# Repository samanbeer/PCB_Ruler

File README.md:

## 30 cm PCB Ruler
https://FORGE.hackclub.com/projects/1713

Why:
- Is is cool, the schooll is coming :O and i dont have a ruler :)

Schematic is randomly connected so it looks good on PCB (not supposed to work :D):

This is a Ruler made as PCB in KiCAD and InkScape(for .svg editing).

- Every design file is in /images folder. 
- And anyone can modify the PCB Ruler by opening This KiCad project in KiCAD v10+
- For direct manufacturing, the gerber files .zip is in /gerbers folder
- Cost around 10 US Dollars :)

Here is JLCPCB cart:

Rendered Image:

## BOM:

| What                             | PRICE    |
| -------------------------------- | -------- |
| PCB (Ruler) + shipping + Customs | 17.15 USD |

*note: I dont need components since I will not solder them on the ruler. The components footprints are for <u>design</u>*

## Builded  project:

Detailed photos:

The precision is great, at the end it has offest just by 0.5mm which is great

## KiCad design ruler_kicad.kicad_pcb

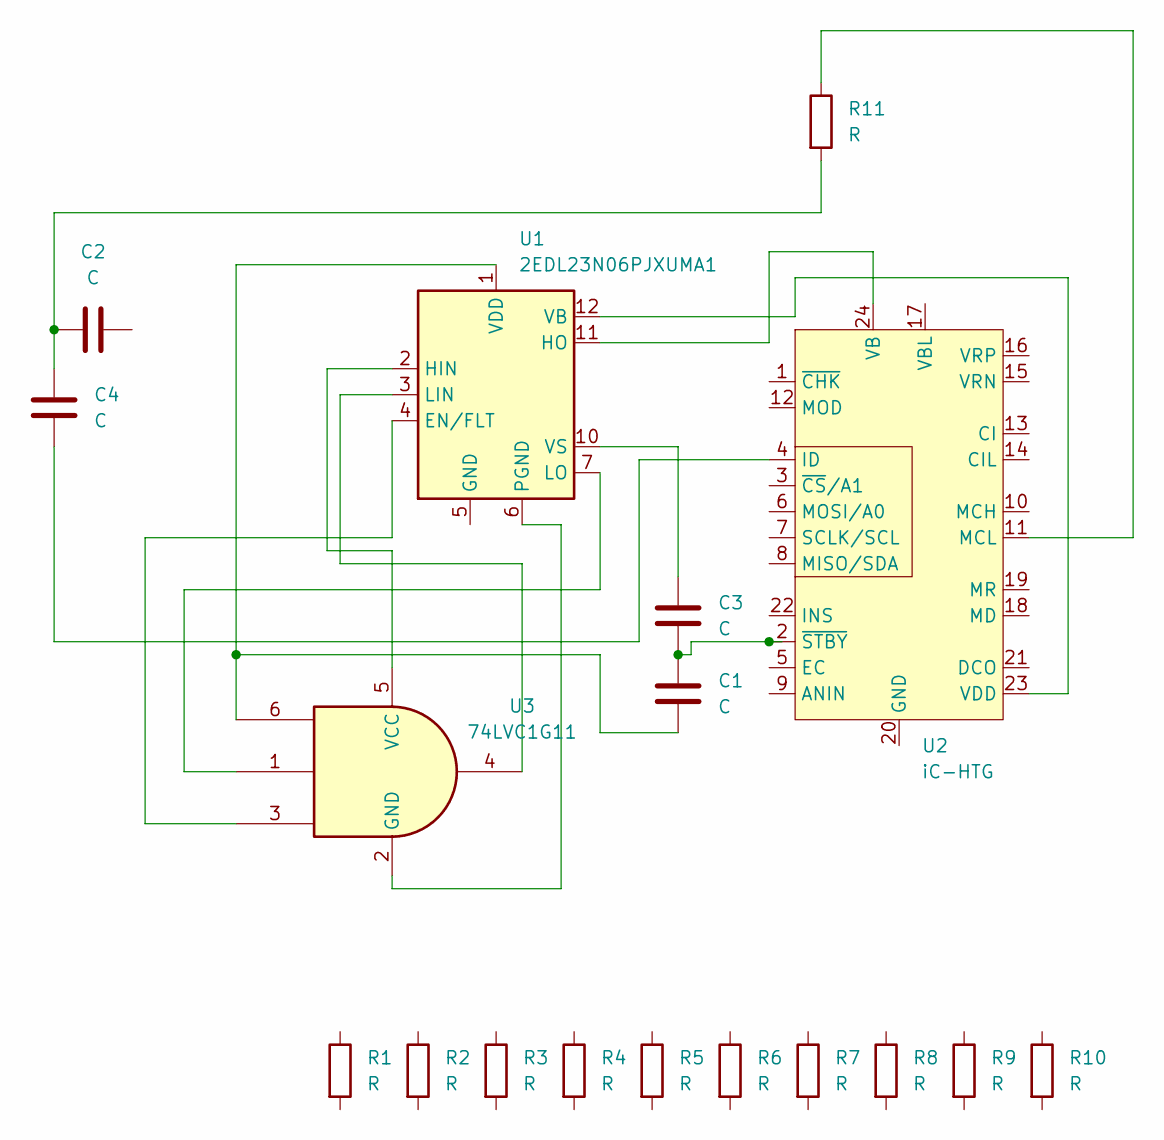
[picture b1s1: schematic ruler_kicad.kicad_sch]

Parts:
C1: C; C_Elec_5x5.4
C2, C3: C; C_1812_4532Metric_Pad1.57x3.40mm_HandSolder
C4: C; C_0805_2012Metric
R1: R; R_0508_1220Metric
R2: R; R_0603_1608Metric
R3: R; R_0612_1632Metric
R4: R; R_0805_2012Metric
R5: R; R_0815_2038Metric
R6: R; R_1020_2550Metric
R7: R; R_1206_3216Metric
R8: R; R_1210_3225Metric
R9: R; R_1812_4532Metric
R10, R11: R; R_2010_5025Metric
U1: 2EDL23N06PJXUMA1; SOIC-14_3.9x8.7mm_P1.27mm
U2: iC-HTG; HVQFN-24-1EP_4x4mm_P0.5mm_EP2.5x2.5mm
U3: 74LVC1G11; SOT-223-6

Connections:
unnamed: C2.2, C4.1, R11.2
unnamed: U1.4 (EN/FLT), U3.3
unnamed: U1.2 (HIN), U3.5 (VCC)
unnamed: U1.11 (HO), U2.24 (VB)
unnamed: U1.3 (LIN), U3.4
unnamed: U1.7 (LO), U3.1
unnamed: U1.6 (PGND), U3.2 (GND)
unnamed: U1.12 (VB), U2.23 (VDD)
unnamed: C1.2, U1.1 (VDD), U3.6
unnamed: C3.1, U1.10 (VS)
unnamed: U2.20 (GND), U2.25 (GND)
unnamed: C4.2, U2.4 (ID)
unnamed: R11.1, U2.11 (MCL)
unnamed: C1.1, C3.2, U2.2 (~STBY)

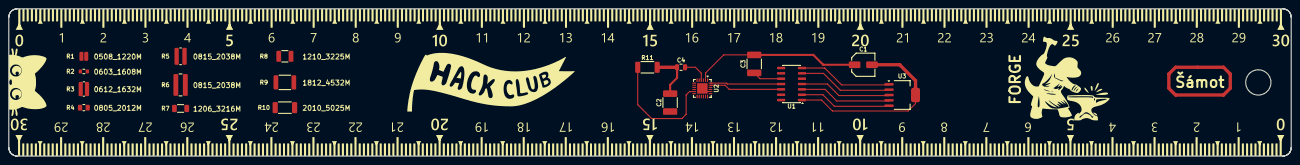
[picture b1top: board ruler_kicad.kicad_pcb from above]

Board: 2 copper layers, 304.9 x 35.0 mm, 18 parts (0 on the bottom side), 14 nets.
